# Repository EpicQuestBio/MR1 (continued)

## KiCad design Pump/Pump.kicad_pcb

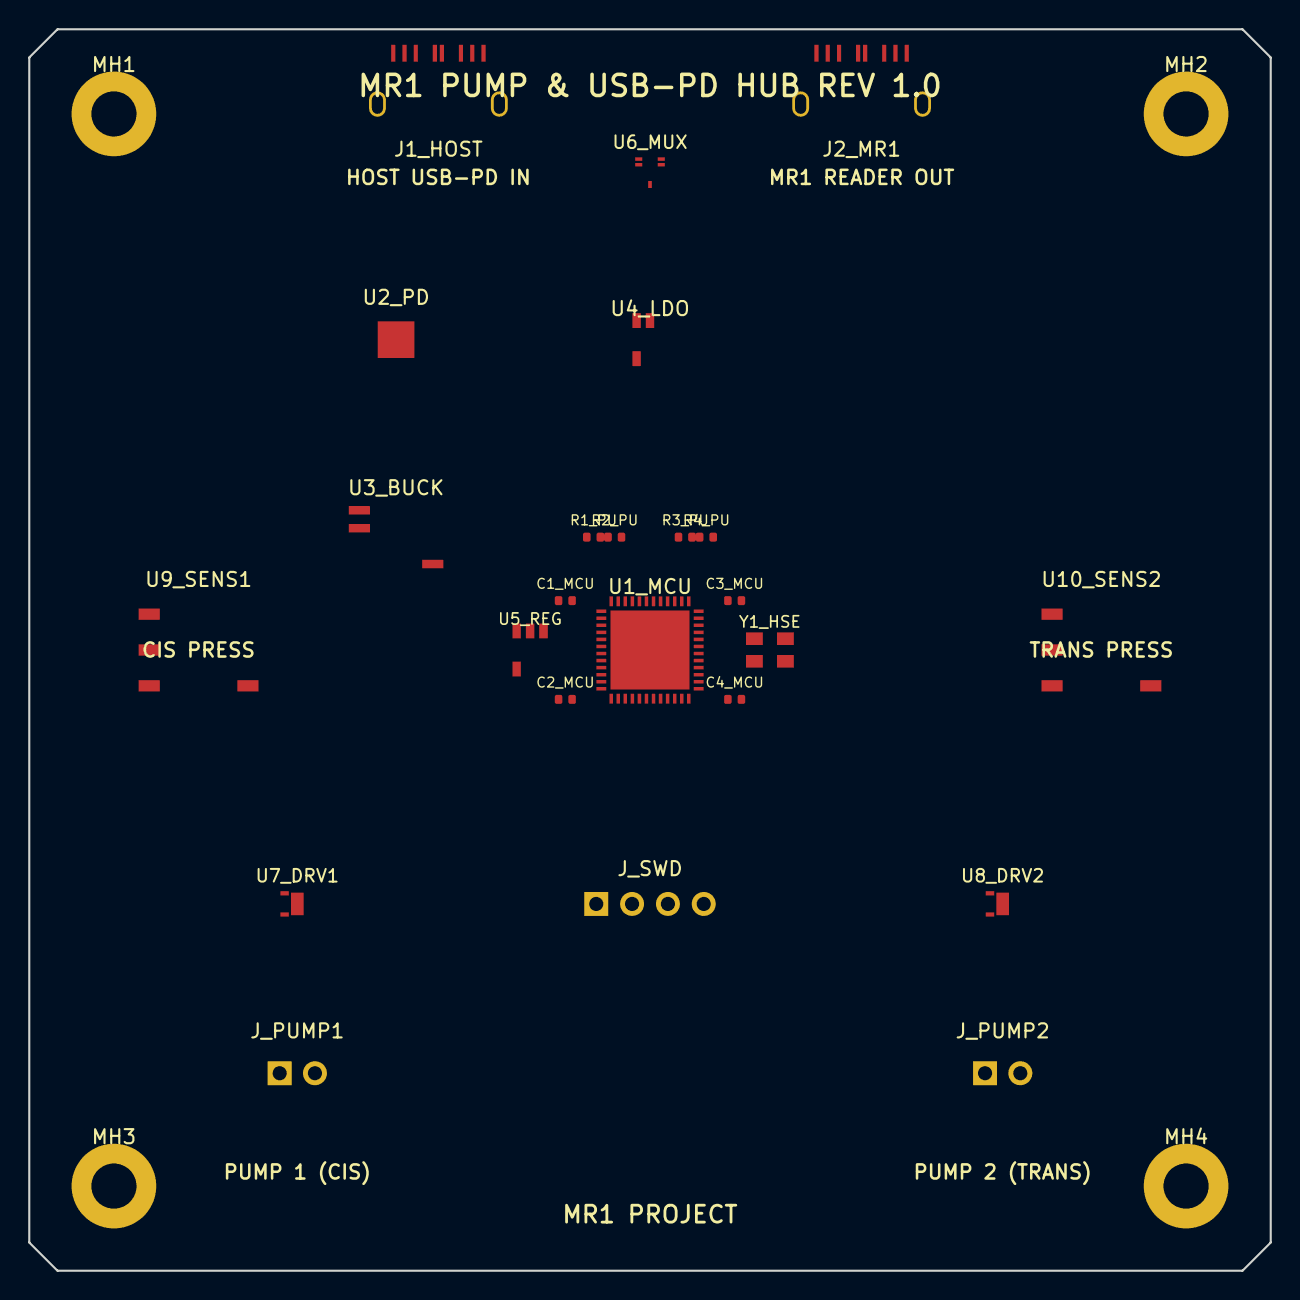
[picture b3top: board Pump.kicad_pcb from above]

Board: 4 copper layers, 88.0 x 88.0 mm, 28 parts (0 on the bottom side), 13 nets, no tracks yet.

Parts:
C1_MCU, C2_MCU, C3_MCU, C4_MCU: 100nF; C_0402_1005Metric
J1_HOST: USB_C_HOST; USB_C_Receptacle_GCT_USB4085
J2_MR1: USB_C_MR1_OUT; USB_C_Receptacle_GCT_USB4085
J_PUMP1, J_PUMP2: PUMP_MOTOR; JST_XH_B2B-XH-A_1x02_P2.50mm_Vertical
J_SWD: PinHeader_1x04_P2.54mm_Vertical
MH1, MH2, MH3, MH4: MountingHole_3.2mm_M3_Pad
R1_PU, R2_PU, R3_PU, R4_PU: 4.7k; R_0402_1005Metric
U1_MCU: STM32G431CBU6; QFN-48-1EP_7x7mm_P0.5mm_EP5.6x5.6mm
U2_PD: STUSB4500; QFN-24-1EP_4x4mm_P0.5mm_EP2.6x2.6mm
U3_BUCK: TPS54302; SOIC-8_3.9x4.9mm_P1.27mm
U4_LDO: LD39050_3V3; SOT-23-5
U5_REG: TLV70233_3V3_ANA; SOT-23-5
U6_MUX: TS3USB221; QFN-10_1.5x2mm_P0.4mm
U7_DRV1, U8_DRV2: DRV8837C; WSON-8-1EP_2x2mm_P0.5mm_EP0.9x1.6mm
U9_SENS1: ABP2_015PG_CIS; Honeywell_ABP_SMD
U10_SENS2: ABP2_005PG_TRANS; Honeywell_ABP_SMD
Y1_HSE: 8.000MHz; Crystal_SMD_3225-4Pin_3.2x2.5mm

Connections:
+3V3: C1_MCU.1, C2_MCU.1, C3_MCU.1, C4_MCU.1, J_SWD.1, R1_PU.1, R2_PU.1, R3_PU.1, R4_PU.1, U1_MCU.9, U1_MCU.24, U1_MCU.36, U1_MCU.48, U4_LDO.5, U5_REG.5, U9_SENS1.2, U10_SENS2.2
+5V_MR1_CLEAN: J2_MR1.A4, J2_MR1.A9, U3_BUCK.5, U4_LDO.1, U5_REG.1, U5_REG.3
+VBUS_PD: J1_HOST.A4, J1_HOST.A9, U3_BUCK.2
GND: C1_MCU.2, C2_MCU.2, C3_MCU.2, C4_MCU.2, J1_HOST.A1, J1_HOST.A12, J1_HOST.SH1, J1_HOST.SH2, J2_MR1.A1, J2_MR1.A12, J2_MR1.SH1, J2_MR1.SH2, J_SWD.4, MH1.1, MH2.1, MH3.1, MH4.1, U1_MCU.8, U1_MCU.23, U1_MCU.35, U1_MCU.47, U1_MCU.49, U2_PD.25, U3_BUCK.1, U4_LDO.2, U5_REG.2, U6_MUX.10, U7_DRV1.4, U7_DRV1.9, U8_DRV2.4, U8_DRV2.9, U9_SENS1.1, U10_SENS2.1, Y1_HSE.2, Y1_HSE.4
HOST_D+: J1_HOST.A6, U6_MUX.1
HOST_D-: J1_HOST.A7, U6_MUX.2
MR1_D+: J2_MR1.A6, U6_MUX.5
MR1_D-: J2_MR1.A7, U6_MUX.6
PRESS_I2C_SCL: R1_PU.2, U9_SENS1.4, U10_SENS2.4
PRESS_I2C_SDA: R2_PU.2, U9_SENS1.3, U10_SENS2.3
SBU1_HOST: J1_HOST.A8, R3_PU.2
SBU2_HOST: J1_HOST.B8, R4_PU.2
VMOTOR: U7_DRV1.1, U8_DRV2.1

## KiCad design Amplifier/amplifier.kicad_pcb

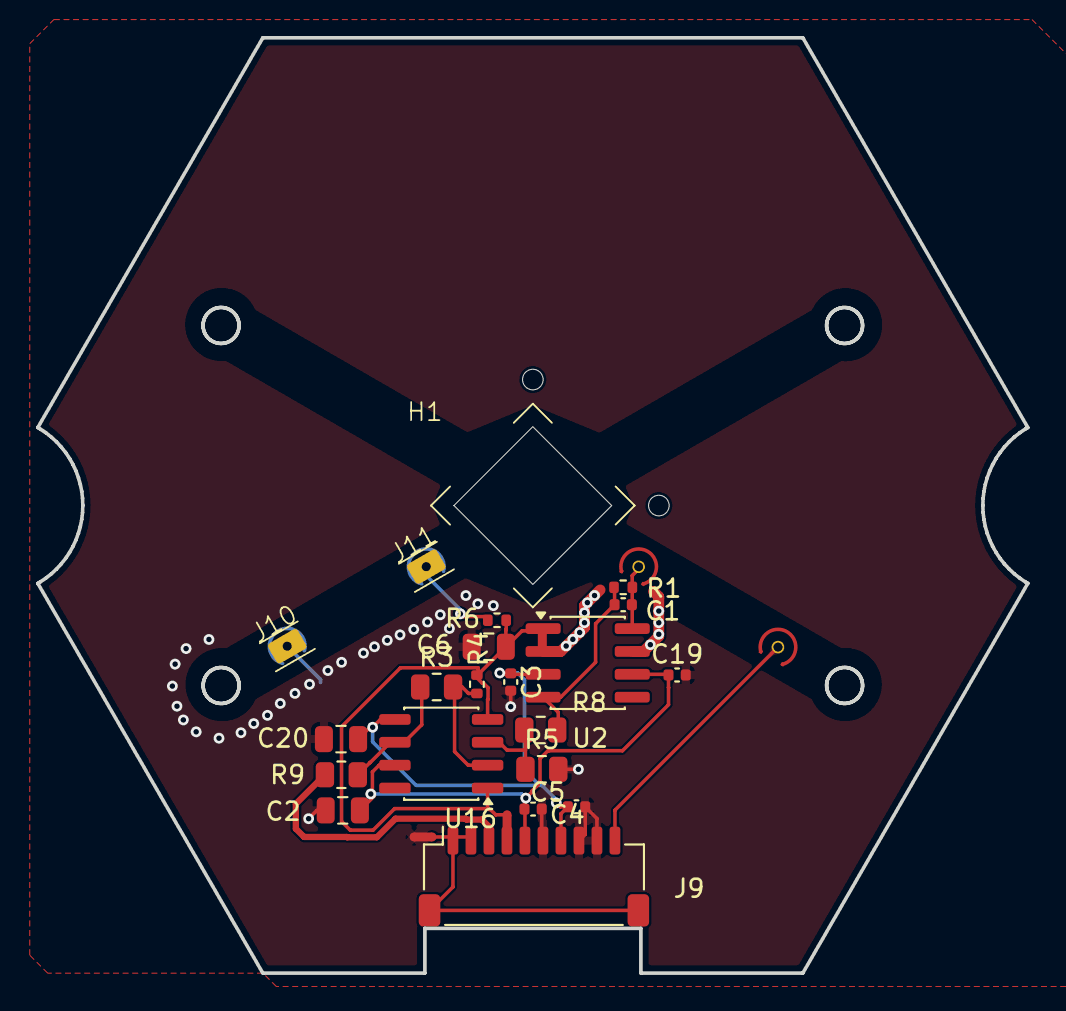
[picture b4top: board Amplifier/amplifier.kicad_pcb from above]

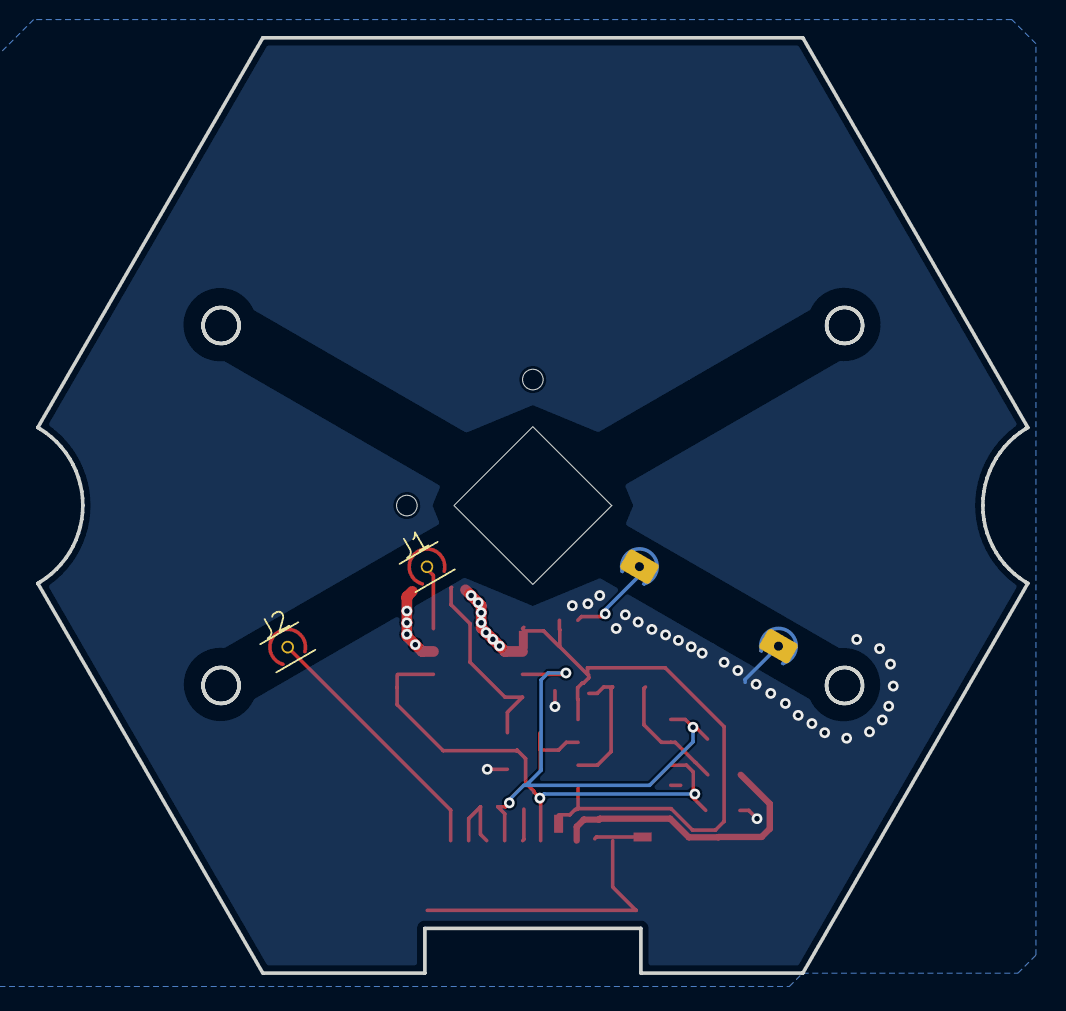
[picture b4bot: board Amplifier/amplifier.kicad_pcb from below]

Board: 2 copper layers, 55.0 x 52.0 mm, 26 parts (2 on the bottom side), 15 nets.

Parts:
C1: 2pF; C_0402_1005Metric
C2, C6, C20: 100nF; C_0805_2012Metric
C3, C19: 100nF; C_0402_1005Metric
C4, C5: 10nF; C_0402_1005Metric
H1: Nanopore; Nanopore holder_recessed
J1, J2, J10, J11: Conn_01x01_Pin; Electrode_Guard_Shield
J9: Conn_01x10; JST_SH_SM10B-SRSS-TB_1x10-1MP_P1.00mm_Horizontal
NT3, NT4, NT5: NetTie_2; NetTie-2_SMD_Pad0.5mm
R1: 1M; R_0402_1005Metric
R3, R5: 1K; R_0805_2012Metric
R4: 100; R_0402_1005Metric
R6: 1K; R_0402_1005Metric
R8, R9: 100; R_0805_2012Metric
U2: LMP7721; SOIC-8_3.9x4.9mm_P1.27mm
U16: LTC6268xS8; SO-8_3.9x4.9mm_P1.27mm

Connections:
/>PORE_AMP: J2.1 (In), J9.10
/GUARD: J1.2 (Ext), NT3.1, U2.2 (NC), U2.7 (NC)
/SHIELD_AMP: J9.1, J9.2, J9.MP (Pin_11), NT4.2
/Signal_AMP: J9.3, R9.1
/Vbias: C6.1, NT3.2, NT5.1, R4.1, R6.1, U2.1 (+), U16.1 (NC), U16.4 (NC)
/Vbias_AMP: J9.4, NT5.2
GNDA: C2.2, C3.2, C4.2, C5.2, C6.2, C19.2, C20.2, J2.2 (Ext), J9.6, J9.8, J9.9, J10.1 (In), J10.2 (Ext), J11.2 (Ext), NT4.1, R5.2
unnamed: C1.1, R1.1, R8.2, U2.4
unnamed: C1.2, J1.1 (In), R1.2, U2.8 (-)
unnamed: J11.1 (In), R6.2
unnamed: R3.1, R9.2, U16.6
unnamed: R5.1, R8.1, U16.3 (+)
unnamed: R3.2, R4.2, U16.2 (-)
VDDA: C2.1, C4.1, C19.1, J9.5, U2.6 (V+), U16.7 (V+)
VSSA: C3.1, C5.1, C20.1, J9.7, U2.3 (V-), U16.5 (V-)

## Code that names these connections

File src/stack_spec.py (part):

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

PINS: Tuple[PinSpec, ...] = (
    PinSpec(1, "GNDA_SHLD", CIS, -18.0, 16.0, "gnd_feed", description="Shield anchor on inlet/outlet manifold ground boundary"),
    PinSpec(2, "WS_CIS_WIDE", CIS, 9.75, -1.75, "signal", ring=GUARD_WIDE, description="Path 2 (200 nm) working sense"),
    PinSpec(3, "GUARD_WIDE", CIS, -20.7, 6.5, "guard_feed", description="Feeds the GUARD_WIDE ring around P2"),
    PinSpec(4, "GUARD_CIS_A", CIS, -0.35, 3.45, "guard_feed", description="Flanking guard A, feeds the GUARD ring around P5"),
    PinSpec(5, "WS_CIS", CIS, 3.9, 3.65, "signal", ring=GUARD, description="Path 1 (sub-5 nm) high-Z electrometer node"),
    PinSpec(6, "GUARD_CIS_B", CIS, -10.65, 11.65, "guard_feed", description="Flanking guard B, feeds the GUARD ring around P5"),
    PinSpec(7, "CE_GNDA", TRANS, -3.195, 15.0, "signal", description="Counter electrode return"),
    PinSpec(8, "RE_TRANS", TRANS, -7.25, 1.35, "signal", description="Trans reference sense"),
    PinSpec(9, ">PORE_AMP", TRANS, 17.45, -5.8, "signal", description="Bias excitation drive"),
    PinSpec(10, "GNDA", TRANS, 11.75, 10.25, "gnd_feed", description="Analog ground fence, feeds GNDA rings"),
    PinSpec(11, "WEEP_SENSE", TRANS, 14.55, -12.45, "signal", description="Weep moat detector"),
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
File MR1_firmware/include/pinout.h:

/*
 * Created by Lawrence R. Kincheloe III / Molecular Reality Corp (2026).
 * Dedicated to the public domain under CC0 1.0 Universal (CC0-1.0).
 * SPDX-License-Identifier: CC0-1.0
 */

/**
 * @file pinout.h
 * @brief Canonical Hardware Pin Mapping for MR1 Nanopore Reader (MR1 Board)
 * 
 * Target MCU: ESP32-S3-MINI-1U
 * Schematics: MR1 (Microcontroller, Ignition, Insturmentation, Power)
 */

#pragma once

#include <stdint.h>

// =============================================================================
// Analog-to-Digital Converter & Readout Route Selection
// =============================================================================
#define PIN_ADC_CNV         11  // Conversion Start / Chip Select (Net: /Insturmentation/DAC_EN)
#define PIN_ADC_SCK         10  // Serial Clock up to 40MHz (Net: /Insturmentation/DAC_CLK)
#define PIN_ADC_SDO          9  // Serial Data Out / MISO (Net: /Microcontroller/DAC_Dout)
#define PIN_ROUTE_SEL        2  // Readout Route Multiplexer Select (Net: /Insturmentation/ROUTE_SEL)

// =============================================================================
// Digital-to-Analog Converter (MCP4822 - U9 on Ignition)
// =============================================================================
#define PIN_DAC_CS           6  // Chip Select (Active Low) (Net: /Ignition/CS_)
#define PIN_DAC_SCK          7  // Serial Clock (Net: /Ignition/SCK)
#define PIN_DAC_SDI          8  // Serial Data In / MOSI (Net: /Ignition/SDI)
#define PIN_DAC_LDAC         5  // Latch Update (Active Low) (Net: /Ignition/LDAC_)

// =============================================================================
// Native USB Interface (J3 Receptacle)
// =============================================================================
#define PIN_USB_DM          19  // USB D- (Net: /Power/D-)
#define PIN_USB_DP          20  // USB D+ (Net: /Power/D+)

// =============================================================================
// USB-C Sideband Use (SBU) & I2C Auto-Polarity Interface
// =============================================================================
#define PIN_USB_SBU1        12  // USB-C SBU1 (Pin A8)
#define PIN_USB_SBU2        13  // USB-C SBU2 (Pin B8)
#define PIN_SBU_MUX_SEL     14  // Hardware cross-multiplexer select (optional)

// =============================================================================
// External Peristaltic Pump Port (J22 - B4B-PH Connector)
// =============================================================================
#define PIN_PUMP_TX         17  // UART TX to Pump Module (J22 Pin 2)
#define PIN_PUMP_RX         47  // UART RX from Pump Module (J22 Pin 3)
#define PUMP_UART_NUM        1  // Hardware UART Port 1

// =============================================================================
// Safety & Leak Detection (Weep Moats & Conductivity Sensor)
// =============================================================================
#define PIN_LEAK_SENSE       1  // Leak detect sense line (Active Low or Analog Threshold)

// =============================================================================
// Host / Debug UART (Optional Header / Programming Console)
// =============================================================================
#define PIN_DEBUG_TX        43  // TXD0
#define PIN_DEBUG_RX        44  // RXD0

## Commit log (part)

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2025-12-23 Add Sentinel Nanopore Reader Rev 11 SCAD file
    - Create `sentinel_nanopore_reader.scad` with the provided Rev 11 design.
    - Optimize housing generation by replacing expensive `minkowski` sum with `linear_extrude` + `offset`.
    - Fix threading incompatibility between Housing and Torque Cap by unifying on BOSL2 `threaded_rod` with a 20mm pitch.
2025-12-23 Redesign housing as split Case/Lid, add feet/interposer
    - Split `Housing_3D` into `Housing_Case` (bottom bucket) and `Housing_Lid` (top plate) to improve 3D printability and allow for a sealed chamber.
    - Add 4x mounting feet to `Housing_Case` with M3 heat-set insert holes.
    - Integrate square `Interposer` module and update `Plate_2_Channel` pocket.
    - Refactor Housing and Cap to use BOSL2 attachments and primitives.
    - Restore internal mounts for Pump and PCB on the Case floor.
    - Standardize thread pitch to 20mm for Torque-Lock mechanism.
2025-12-23 Add support for 1/4 inch NPT compression fittings to Housing_Lid and introduce Bottom_Pusher_Plate
    - Modified `Housing_Lid` to replace the central cutout with a solid shelf.
    - Added 4x bosses on the underside of `Housing_Lid` with 1/4" NPT threads (approx).
    - Created `Bottom_Pusher_Plate` module (TPU) with O-ring seats for sealing.
    - Updated cartridge stack (`Plate_1`, `Plate_2`, `Plate_3`, `Gasket`) to support 4 fluid ports (Bottom Flush & Top Flush).
    - Updated port radius to 20mm and angles to ±30°/150°/210° to fit larger fittings.
    - Added `Bottom_Pusher_Plate_STL` to output options.
2025-12-24 adding json visuialization and e2e testing
2025-12-25 Correct BOSL2 attach coordinates for ports and connectors
    Fixed floating components and failing boolean operations by:
    1. Removing incorrect Z-axis offsets (`pump_h/2`, `lid_thick/2`) in `attach()` blocks that caused ports to detach from walls.
    2. Removing incorrect rotations (`rotate([0,90,0])`, `rotate([90,0,0])`) to ensure ports and cutouts align with the surface normal.
    3. Standardizing side port translations.
    This resolves issues with "ghost holes" (red cylinders) failing to cut the housing and fluid ports floating in mid-air.
2025-12-30 Implement Hexagonal Cartridge Stack with Potted Kelvin Carrier
    - Refactored cartridge stack components to Hexagonal geometry (60mm diameter).
    - Implemented `PCB_Kelvin_Insert` with central potting puck, mesh, and silver ribbon electrodes.
    - Updated `Carrier_Frame_Hex` to house the rectangular PCB insert.
    - Updated `Housing_Lid_Reader` with hexagonal socket for self-indexing and 5-pin linear pogo layout.
    - Added `O_Ring_Inner` modules for sealing the potting puck.
    - Corrected assembly logic for Top-Down pogo pin access.
2026-01-01 minor update, lots of little changes,
2026-01-08 Add KiCad specific patterns to .gitignore
2026-01-09 Refactor Sentinel Nanopore Reader OpenSCAD code into modular files
    This change breaks down the monolithic `sentinel_nanopore_reader.scad` file into smaller, more manageable modules:
    - `constants.scad`: Global variables and BOSL2 includes.
    - `modules/common.scad`: Shared utility modules.
    - `modules/cartridge.scad`: Cartridge stack components.
    - `modules/housing_pump.scad`: Pump module housing.
    - `modules/housing_reader.scad`: Reader module housing.
2026-01-15 Fix Cartridge Stack colors and attachments
    Refactored `PCB_Active_Stack_3D` and `Gasket_Low_Dead_Volume_3D` to use the BOSL2 `attachable` wrapper correctly.
    - `PCB_Active_Stack_3D`: Uses `attachable` to define a phantom attachment geometry while rendering only the internal PCB components. This prevents a solid cylinder from obscuring the components and r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
    - `Gasket_Low_Dead_Volume_3D`: Moves the `children()` call outside the internal `diff` block, placing it as a direct child of `attachable`. This ensures robust attachment propagation and prevents unn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
    - Restores proper color visibility for the Cartridge Stack ass
2026-01-18 Update PCB position to be on top of the lid and remove mounting holes
2026-01-18 Fix floating PCB standoffs in Housing_Lid_Reader
    - Moved standoffs from rim level (-lid_thick) to ceiling level (-ceiling_thick).
    - Removed rotation to ensure correct downward orientation from ceiling.
    - Fixed screw hole attachment to properly cut into the standoff from the bottom.
2026-01-18 Refactor PCB_Active_Stack_3D to remove union wrapper
    Replaced the explicit union() around Nanopore_Carrier and PCB_Rigid_Active with a helper module PCB_Active_Stack_Parts. This allows the two boards to exist as separate objects in the OpenSCAD tree wh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
2026-01-18 Fix Pump Module port penetration depth
    Increased the cut depth for DIN, USB-C, and Barrel Jack ports on the Housing_Pump_Case from wall*3 to wall*10. This ensures the cutouts fully penetrate the thick wall of the housing, resolving the is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
2026-01-18 Restore gasket verification tests
    - Restored `tests/test_gasket_plan.scad` for visual verification.
    - Restored `tests/verify_gasket_integration.js` for targeted DXF rendering checks.
2026-01-29 Fix export script Windows compatibility and VFS paths
    Updated `scripts/export_all.js` to force forward slashes for Virtual File System paths, resolving `Can't open include file` errors on Windows.
    The script now correctly mounts `BOSL2` and `modules` into the WASM instance regardless of the host OS separator.
    Also confirmed redundant `projection()` calls were removed from `sentinel_nanopore_reader.scad` in the previous step.
2026-01-31 Fix Torque Cap ribs/ceiling and Main PCB position
    - Remove ribs from finger slots in Torque Cap to prevent interference.
    - Add ceiling to Torque Cap by limiting internal clearance cut height.
    - Move Main Reader PCB to internal position (underside of lid) to fix visual protrusion.
2026-01-31 Rotate pump ports to horizontal alignment and fix blue tube routing
    - Modified `modules/housing_pump.scad`: Changed port generation loop to use `x_pos` (horizontal) instead of `y_pos` (vertical) on Left/Right faces, aligning them at Y=+/-20mm.
    - Modified `sentinel_nanopore_reader.scad`: Updated the "DeepSkyBlue" external tubing visualization to route around the back of the device, preventing clipping through the housing case.
    - Verified changes by compilation and code review.
2026-02-01 Refine Plate 3 cutout to strictly conform to PCB component layout
    Replaces the generic convex hull cutout in `Plate_3_Top_Hex` with a precise union of hulls targeting the Top OpAmp and Bottom Component Cluster (JST, OpAmp 2, Filters). This ensures the cutout "hugs"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
    Calculated component bounds from `PCB_Rigid_Active` and applied ~1mm clearance.
2026-02-01 Update PCB pad visualization to Gold pads with Silver ribbons
    - Updated `PCB_Rigid_Active` in `modules/cartridge.scad`:
    - Reverted bottom pads base color to Gold (all 4 pads are now Gold).
    - Added a 0.8mm wide Silver ribbon strip to each of the 4 pads.
    - Adjusted Z-offsets of the ribbons (+0.06 for top, -0.06 for bottom) to ensure they render visibly on top of the pads.
2026-02-01 Add missing fluid and electrode ports to Plate_3_Top_Hex
    This change adds missing pass-through holes to the `Plate_3_Top_Hex` module (often referred to as the "Top Cap" of the stack).
    - Added clearance holes for `angle_fluid_in_bot` and `angle_fluid_out_bot` to match the 4-port pattern found on other stack layers.
    - Added a clearance hole for `angle_elec_cis` (Top Electrode) which was previously missing in the Hex version but present in the legacy Round version.
    This addresses the issue where the top plate had an incomplete hole pattern relative to the rest of the cartridge stack. Note: Bolt holes are explicitly excluded as the stack does not use bolts.
2026-02-19 Reduce Torque Cap size and add ergonomic grips
    - Updated `constants.scad`: Reduced `neck_od` from 90mm to 75mm to shrink the overall cap and thread size.
    - Updated `modules/torque_cap.scad`:
    - Changed `Torque_Cap_Outer` to use `rounding=2` (2mm fillet) on both top and bottom edges.
    - Added 12 vertical recessed grip indentations (cylindrical cuts) to the outer perimeter, offset by 15 degrees to interleave with existing finger slots.
    - Verified changes using a simplified render test script (`test_render_single.js` with `openscad-wasm`).
2026-02-19 updated cap rib finger height
2026-02-20 Fix Housing_Reader_Lid_STL export failure due to 2D/3D mixing.
    Replaced 2D `circle` subtraction with 3D `cylinder` in `Housing_Lid_Reader` to resolve "Mixing 2D and 3D objects" warning which caused the main body to disappear.
    Added 0.1mm overlap to PCB Mounts and Indexing Lip to resolve CGAL assertion violations during union operations.
    Verified with regression script `reproduce_issue.js` showing successful generation and reasonable file size (2.5MB).
2026-03-01 Update Torque_Cap_Inner retention flange to be rounded and protrude 0.2mm
    - Changed the `cyl` diameter for the retention flange from `neck_od + 8` to `neck_od + 6.4`.
    - Added `rounding=1` to the `cyl` module to make the flange edges round.
    - These changes ensure the flange only protrudes about 0.2mm radially past the torque triangles, matching the design request.
2026-03-04 fix: thicken pump lid to support deeper foot dimples
    - Added `pump_lid_thick` constant (`wall + 2`) to ensure 7mm total thickness for the pump lid.
    - Modified `modules/housing_pump.scad` to use the thicker `pump_lid_thick` so the 4mm deep dimple doesn't poke out or get too thin.
    - Updated main assembly translations (`test_render.scad`, `test_verify.scad`, `sentinel_nanopore_reader.scad`) to use `pump_lid_thick` instead of `wall` for correct stacking height calculations.
2026-03-13 updated reader
2026-03-15 fix: Resolve remaining nonplanar face export errors in pump case
    - Adjusts the `Housing_Pump_Case` handle `path_sweep` to fully penetrate the housing wall (`translate([0, 0, -1])`) and sets a lower polygon count (`$fn=16`) to mitigate "PolySet has nonplanar faces"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
    - Adds `overlap=0.1` to `attach()` boundaries (LEFT, RIGHT, TOP, FRONT, BACK) to resolve perfectly coincident vertices.
    - Lowers poly counts on edge components like Lid Mounts (`$fn=16`) to simplify intersection mesh.
2026-03-20 Revert "feat: Ratchet-style torque limiter flex arm"
2026-03-27 docs: add 1/8" hose barb bulkhead luer to BOM
    Added Item 96550 / Ark-Plas LJX39-PP0 (1/8" Hose Barb x Female Threaded Natural Polypropylene Bulkhead Luer) to the Bill of Materials table in BOM.md.
2026-03-28 Enlarge fluid routing holes on reader lid top to 10mm
